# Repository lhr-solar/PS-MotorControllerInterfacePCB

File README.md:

# PS - Motor Controller Interface

## Board Specification
- Handles power conversion and fan control for the Prohelion WaveSculptor 22.

## Confluence
- https://cloud.wikis.utexas.edu/wiki/spaces/LHRSOLAR/pages/484769832/Motor+Controller+Interface+Board

## File Structure
- Core
- Drivers
- Tasks
- Tests
- Embedded-Sharepoint
- Makefile

## Building / Testing
- nix develop ./Embedded-Sharepoint (from firmware directory)
- Run ``` make ``` to build main files.
- Run ``` make TEST=test_name ```, where ```test_name``` is the name of the test without the .c suffix.

## Flashing (UART)
- Make sure switch is set to EXT, then flash via UART (``` make flash-uart ```). 
- Set the switch to USR then press RESET button to execute code.

- Note: flashing to this board (not psom issue) is really difficult. have fun spamming reset
## Flashing (ST-Link)
- To flash an STM32 microcontroller using an ST-Link, wire the device to the ST-Link (SWDIO, SWCLK, GND, 3.3V) and use software like STM32CubeProgrammer or STM32 ST-LINK Utility to erase, load, and verify the .bin or .hex firmware file.

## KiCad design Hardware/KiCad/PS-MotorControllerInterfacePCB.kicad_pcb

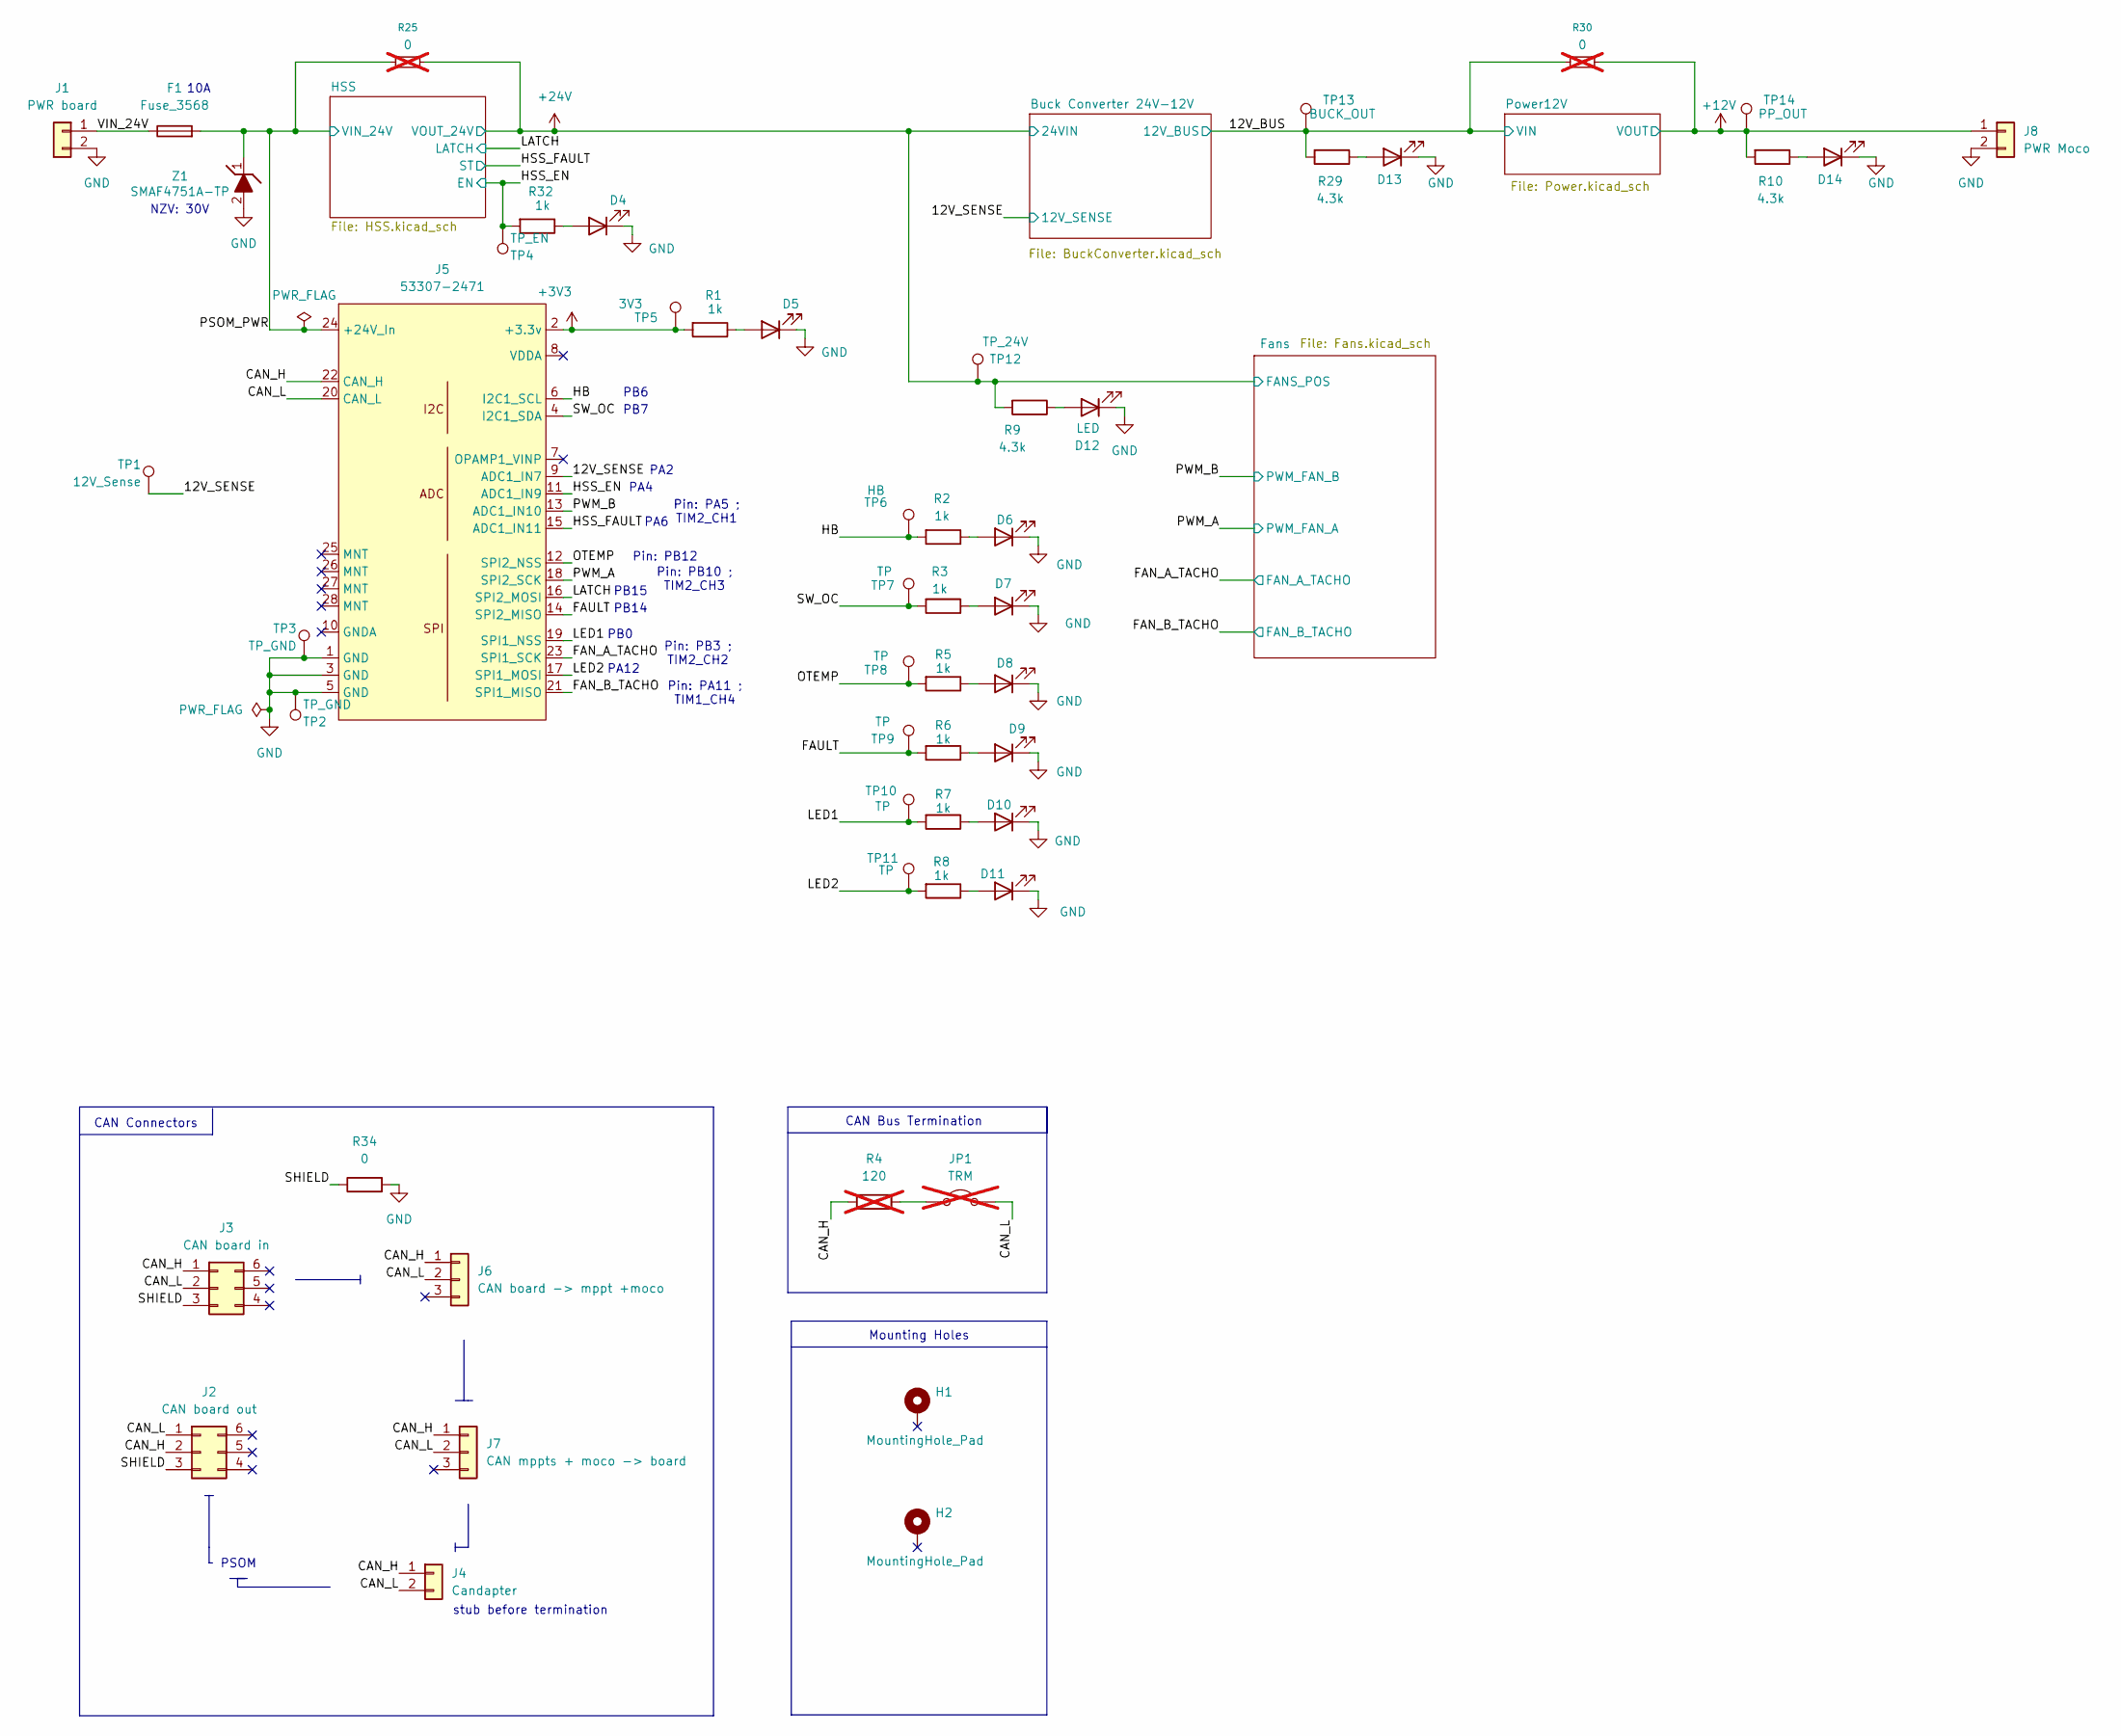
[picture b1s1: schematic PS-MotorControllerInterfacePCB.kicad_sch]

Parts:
D4, D5, D6, D7, D8, D9, D10, D11, D12, D13, D14: LED; LED_0603_1608Metric; LCSC C84263
F1: Fuse_3568; FUSE_3568; Mouser P/N 534-3568
H1, H2: MountingHole_Pad; MountingHole_3.2mm_M3_Pad_TopBottom
J1: PWR board; 105313-2102
J2: CAN board out; 105314-1306
J3: CAN board in; 105314-1306
J4: Candapter; 105313-2102
J5: 53307-2471; PeripheralSOM
J6: CAN board -> mppt +moco; 105313-1103
J7: CAN mppts + moco -> board; 105313-1103
J8: PWR Moco; 105313-2102
JP1: TRM; PinHeader_1x02_P2.54mm_Vertical; Mouser Part Number M7567-05; not fitted
R1, R2, R3, R5, R6, R7, R8, R32: 1k; R_0603_1608Metric_Pad0.98x0.95mm_HandSolder; Manufacturer_Part_Number CRCW06034K30FKEA; LCSC C21190
R4: 120; R_0603_1608Metric_Pad0.98x0.95mm_HandSolder; Manufacturer_Part_Number CRCW0603120RFKEC; LCSC C22787; not fitted
R9, R10, R29: 4.3k; R_0603_1608Metric_Pad0.98x0.95mm_HandSolder; Manufacturer_Part_Number CRCW06034K30FKEA; LCSC C2907165
R25, R30: 0; R_0603_1608Metric_Pad0.98x0.95mm_HandSolder; LCSC C21189; not fitted
R34: 0; R_0603_1608Metric_Pad0.98x0.95mm_HandSolder; LCSC C21189
TP1: 12V_Sense; TestPoint_Keystone_5000-5004_Miniature
TP2: TP_GND; PinHeader_1x01_P2.54mm_Vertical
TP3: TP_GND; TestPoint_Keystone_5000-5004_Miniature
TP4: TP_EN; TestPoint_Keystone_5000-5004_Miniature
TP5: 3V3; TestPoint_Keystone_5000-5004_Miniature
TP6: HB; TestPoint_Keystone_5000-5004_Miniature
TP7, TP8, TP9, TP10, TP11: TP; TestPoint_Keystone_5000-5004_Miniature
TP12: TP_24V; TestPoint_Keystone_5000-5004_Miniature
TP13: BUCK_OUT; TestPoint_Keystone_5000-5004_Miniature
TP14: PP_OUT; TestPoint_Keystone_5000-5004_Miniature
Z1: SMAF4751A-TP; SODFL5026X125N; Mouser Part Number 833-SMAF4751A-TP

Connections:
+3V3: J5.2 (+3.3v), R1.2, TP5.1; also elsewhere on the board
+12V: J8.1, R10.2, R30.2, TP14.1; also elsewhere on the board
+24V: R9.2, R25.2, TP12.1; also elsewhere on the board
/12V_BUS: R29.2, R30.1, TP13.1; also elsewhere on the board
/12V_SENSE: J5.9 (ADC1_IN7), TP1.1; also elsewhere on the board
/CAN_H: J2.2, J3.1, J4.1, J5.22 (CAN_H), J6.1, J7.1, R4.1
/CAN_L: J2.1, J3.2, J4.2, J5.20 (CAN_L), J6.2, J7.2, JP1.2 (B)
/FAN_A_TACHO: J5.23 (SPI1_SCK); also elsewhere on the board
/FAN_B_TACHO: J5.21 (SPI1_MISO); also elsewhere on the board
/FAULT: J5.14 (SPI2_MISO), R6.2, TP9.1
/HB: J5.6 (I2C1_SCL), R2.2, TP6.1
/HSS_EN: J5.11 (ADC1_IN9), R32.2, TP4.1; also elsewhere on the board
/HSS_FAULT: J5.15 (ADC1_IN11); also elsewhere on the board
/LATCH: J5.16 (SPI2_MOSI); also elsewhere on the board
/LED1: J5.19 (SPI1_NSS), R7.2, TP10.1
/LED2: J5.17 (SPI1_MOSI), R8.2, TP11.1
/OTEMP: J5.12 (SPI2_NSS), R5.2, TP8.1
/PSOM_PWR: F1.2, J5.24 (+24V_In), R25.1, Z1.1 (K); also elsewhere on the board
/PWM_A: J5.18 (SPI2_SCK); also elsewhere on the board
/PWM_B: J5.13 (ADC1_IN10); also elsewhere on the board
/SHIELD: J2.3, J3.3, R34.1
/SW_OC: J5.4 (I2C1_SDA), R3.2, TP7.1
/VIN_24V: F1.1, J1.1
GND: D4.1 (K), D5.1 (K), D6.1 (K), D7.1 (K), D8.1 (K), D9.1 (K), D10.1 (K), D11.1 (K), D12.1 (K), D13.1 (K), D14.1 (K), J1.2, J5.1 (GND), J5.3 (GND), J5.5 (GND), J8.2, R34.2, TP2.1, TP3.1, Z1.2 (A); also elsewhere on the board
unnamed: D4.2 (A), R32.1
unnamed: D5.2 (A), R1.1
unnamed: D6.2 (A), R2.1
unnamed: D7.2 (A), R3.1
unnamed: D8.2 (A), R5.1
unnamed: D9.2 (A), R6.1
unnamed: D10.2 (A), R7.1
unnamed: D11.2 (A), R8.1
unnamed: D12.2 (A), R9.1
unnamed: D13.2 (A), R29.1
unnamed: D14.2 (A), R10.1
unnamed: JP1.1 (A), R4.2

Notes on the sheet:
NZV: 30V
PSOM
CAN Bus Termination
PA4
PB15
Pin: PB10 ; TIM2_CH3
PB6
10A
Pin: PA11 ; TIM1_CH4
PB7
CAN Connectors
Mounting Holes
Pin: PB12
stub before termination
Pin: PA5 ; TIM2_CH1
Pin: PB3 ; TIM2_CH2
PA2
PA12
PB14
PA6
PB0

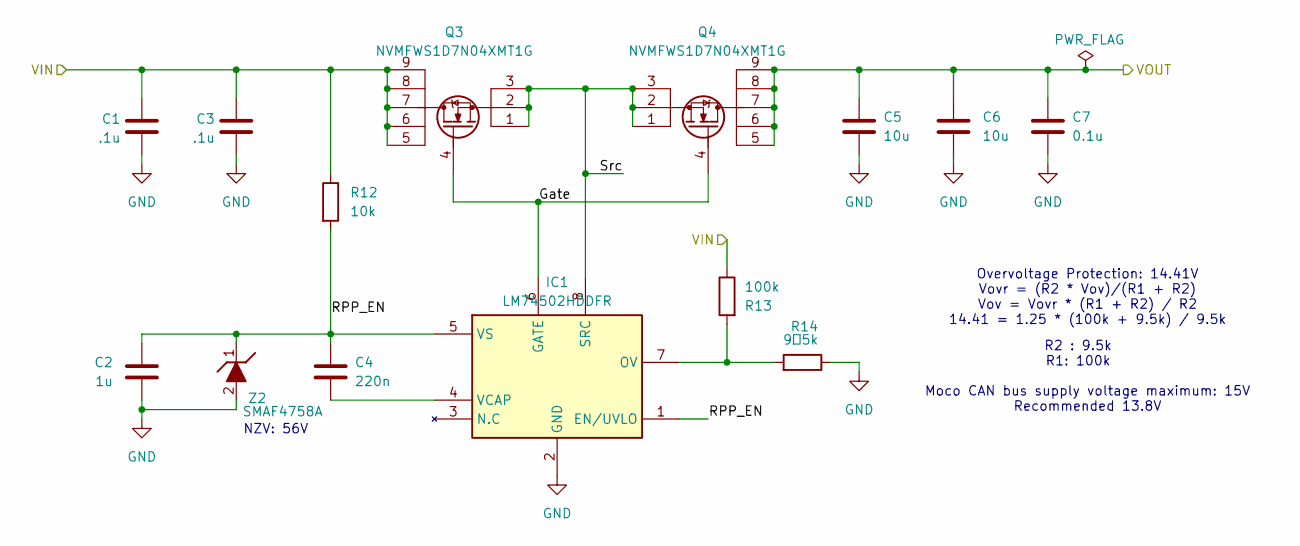
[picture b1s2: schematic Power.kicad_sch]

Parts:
C1, C3: .1u; C_0603_1608Metric_Pad1.08x0.95mm_HandSolder; Manufacturer_Part_Number 06035C223K4T4A; LCSC C14663
C2: 1u; C_0603_1608Metric_Pad1.08x0.95mm_HandSolder; Manufacturer_Part_Number MLASU168SB5105KTNA01; LCSC C15849
C4: 220n; C_0603_1608Metric_Pad1.08x0.95mm_HandSolder; Manufacturer_Part_Number MSASU168SB7224KTNB25; LCSC C344195
C5, C6: 10u; C_0603_1608Metric_Pad1.08x0.95mm_HandSolder; Manufacturer_Part_Number GRM21BR61H106KE43K; LCSC C1691
C7: 0.1u; C_0603_1608Metric_Pad1.08x0.95mm_HandSolder; Manufacturer_Part_Number MLASH168SB7104KTNA01; LCSC C14663
IC1: LM74502HDDFR; SOT65P280X110-8N; Mouser Part Number 595-LM74502HDDFR
Q3, Q4: NVMFWS1D7N04XMT1G; NVMFWS3D0P04M8LT1G; LCSC P/N C133142
R12: 10k; R_0805_2012Metric_Pad1.20x1.40mm_HandSolder; Manufacturer_Part_Number CRCW060310K0FKEI; LCSC C702829
R13: 100k; R_0603_1608Metric_Pad0.98x0.95mm_HandSolder; Manufacturer_Part_Number CRCW0603100KFKEE; LCSC C25803
R14: 9。5k; R_0603_1608Metric_Pad0.98x0.95mm_HandSolder
Z2: SMAF4758A; SODFL5026X125N; Manufacturer_Part_Number SMAF4749A-TP; LCSC C183490

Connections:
+12V: C5.1, C6.1, C7.1, Q4.5, Q4.6, Q4.7, Q4.8, Q4.9; also elsewhere on the board
/12V_BUS: C1.2, C3.2, Q3.5, Q3.6, Q3.7, Q3.8, Q3.9, R12.1, R13.1; also elsewhere on the board
/Power12V/Gate: IC1.6 (GATE), Q3.4, Q4.4
/Power12V/RPP_EN: C2.2, C4.1, IC1.1 (EN/UVLO), IC1.5 (VS), R12.2, Z2.1 (K)
/Power12V/Src: IC1.8 (SRC), Q3.1, Q3.2, Q3.3, Q4.1, Q4.2, Q4.3
GND: C1.1, C2.1, C3.1, C5.2, C6.2, C7.2, IC1.2 (GND), R14.1, Z2.2 (A); also elsewhere on the board
unnamed: IC1.7 (OV), R13.2, R14.2
unnamed: C4.2, IC1.4 (VCAP)

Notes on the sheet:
Overvoltage Protection: 14.41V Vovr = (R2 * Vov)/(R1 + R2) Vov = Vovr * (R1 + R2) / R2 14.41 = 1.25 * (100k + 9.5k) / 9.5k
Moco CAN bus supply voltage maximum: 15V Recommended 13.8V
R2 : 9.5k R1: 100k
NZV: 56V

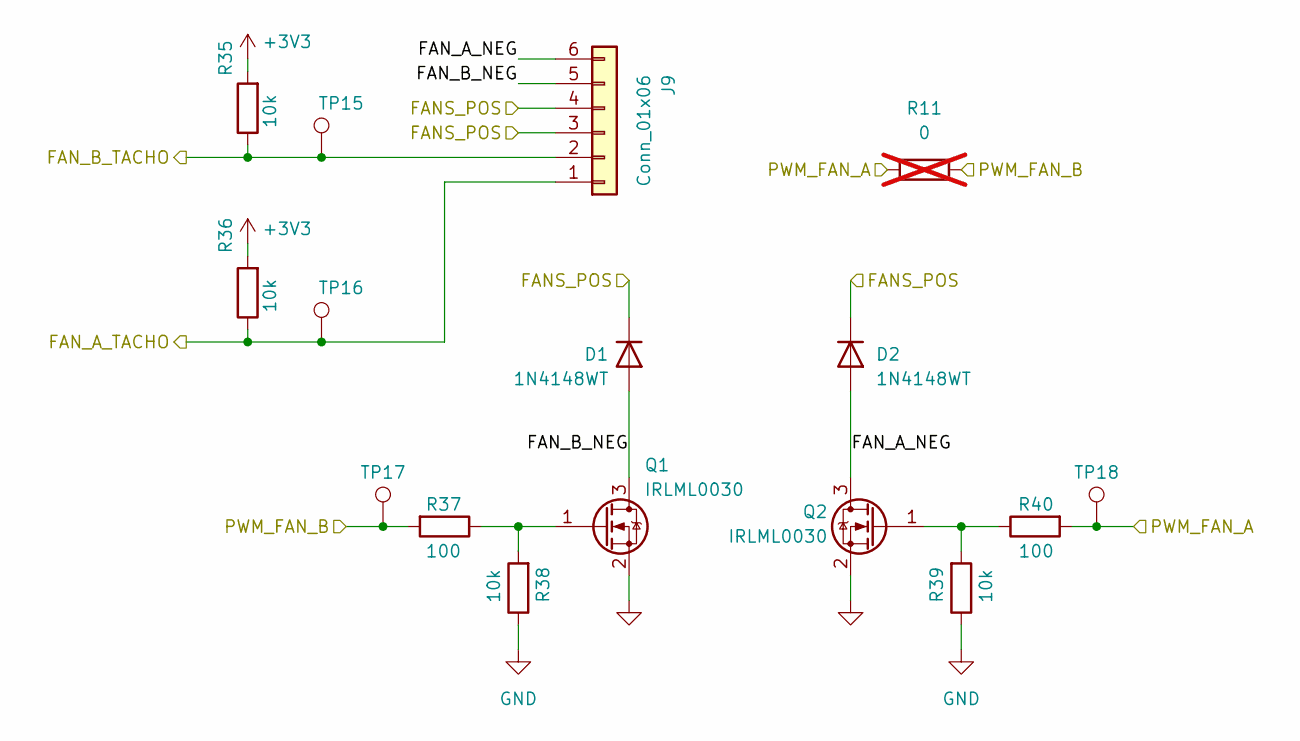
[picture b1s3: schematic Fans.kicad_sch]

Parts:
D1, D2: 1N4148WT; SODFL4724X108N; Manufacturer_Part_Number NCD0603R1; Mouser Part Number 637-1N4148WT
J9: Conn_01x06; 105313-1106; Mouser Part Number 538-105309-1206
Q1, Q2: IRLML0030; SOT-23; LCSC C67272
R11: 0; R_0603_1608Metric_Pad0.98x0.95mm_HandSolder; Manufacturer_Part_Number CRCW06030000Z0EE; LCSC C21189; not fitted
R35, R36, R38, R39: 10k; R_0603_1608Metric_Pad0.98x0.95mm_HandSolder; Manufacturer_Part_Number CRCW060310K0FKEI; LCSC C25804
R37, R40: 100; R_0603_1608Metric_Pad0.98x0.95mm_HandSolder; Manufacturer_Part_Number CRCW0603120RFKEC; LCSC C22356636
TP15, TP16: TP_PWM_B; TestPoint_Pad_1.0x1.0mm
TP17: TP_PWM_A; PinHeader_1x01_P2.54mm_Vertical
TP18: TP_PWM_B; PinHeader_1x01_P2.54mm_Vertical

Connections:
+3V3: R35.2, R36.2; also elsewhere on the board
+24V: D1.1 (K), D2.1 (K), J9.3, J9.4; also elsewhere on the board
/FAN_A_TACHO: J9.1, R36.1, TP16.1; also elsewhere on the board
/FAN_B_TACHO: J9.2, R35.1, TP15.1; also elsewhere on the board
/Fans/FAN_A_NEG: D2.2 (A), J9.6, Q2.3 (D)
/Fans/FAN_B_NEG: D1.2 (A), J9.5, Q1.3 (D)
/PWM_A: R11.1, R40.2, TP18.1; also elsewhere on the board
/PWM_B: R11.2, R37.2, TP17.1; also elsewhere on the board
GND: Q1.2 (S), Q2.2 (S), R38.1, R39.1; also elsewhere on the board
unnamed: Q1.1 (G), R37.1, R38.2
unnamed: Q2.1 (G), R39.2, R40.1

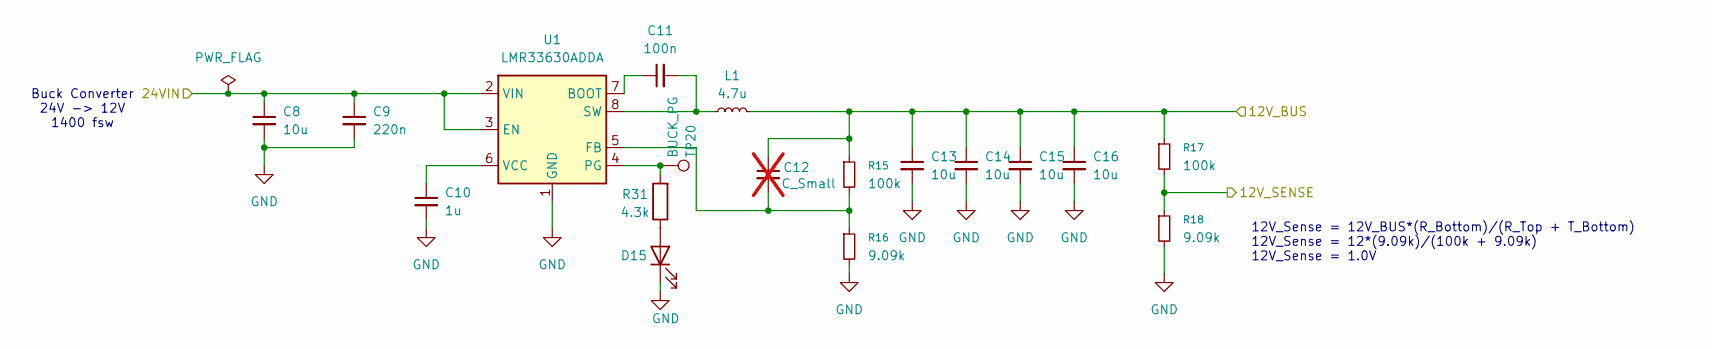
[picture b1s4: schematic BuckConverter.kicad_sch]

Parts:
C8, C13, C14, C15, C16: 10u; C_0603_1608Metric_Pad1.08x0.95mm_HandSolder; LCSC C1691
C9: 220n; C_0603_1608Metric_Pad1.08x0.95mm_HandSolder; LCSC C344195
C10: 1u; C_0603_1608Metric_Pad1.08x0.95mm_HandSolder; LCSC C15849
C11: 100n; C_0603_1608Metric_Pad1.08x0.95mm_HandSolder; LCSC C14663
C12: C_Small; C_0603_1608Metric_Pad1.08x0.95mm_HandSolder; not fitted
D15: LED; LED_0603_1608Metric; LCSC C84263
L1: 4.7u; IND-SMD_L5.0-W5.0; LCSC C354606
R15, R17: 100k; R_0603_1608Metric_Pad0.98x0.95mm_HandSolder; LCSC C25803
R16, R18: 9.09k; R_0603_1608Metric_Pad0.98x0.95mm_HandSolder
R31: 4.3k; R_0603_1608Metric_Pad0.98x0.95mm_HandSolder; Manufacturer_Part_Number CRCW06034K30FKEA; LCSC C2907165
TP20: BUCK_PG; TestPoint_Keystone_5000-5004_Miniature
U1: LMR33630ADDA; Texas_HSOP-8-1EP_3.9x4.9mm_P1.27mm_ThermalVias; LCSC C841384

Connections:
+24V: C8.1, C9.1, U1.2 (VIN), U1.3 (EN); also elsewhere on the board
/12V_BUS: C12.1, C13.1, C14.1, C15.1, C16.1, L1.2, R15.1, R17.1; also elsewhere on the board
/12V_SENSE: R17.2, R18.1; also elsewhere on the board
GND: C8.2, C9.2, C10.2, C13.2, C14.2, C15.2, C16.2, D15.1 (K), R16.2, R18.2, U1.1 (GND), U1.9 (GND); also elsewhere on the board
unnamed: D15.2 (A), R31.1
unnamed: C11.1, U1.7 (BOOT)
unnamed: C12.2, R15.2, R16.1, U1.5 (FB)
unnamed: R31.2, TP20.1, U1.4 (PG)
unnamed: C11.2, L1.1, U1.8 (SW)
unnamed: C10.1, U1.6 (VCC)

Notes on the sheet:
12V_Sense = 12V_BUS*(R_Bottom)/(R_Top + T_Bottom) 12V_Sense = 12*(9.09k)/(100k + 9.09k) 12V_Sense = 1.0V
Buck Converter 24V -> 12V 1400 fsw

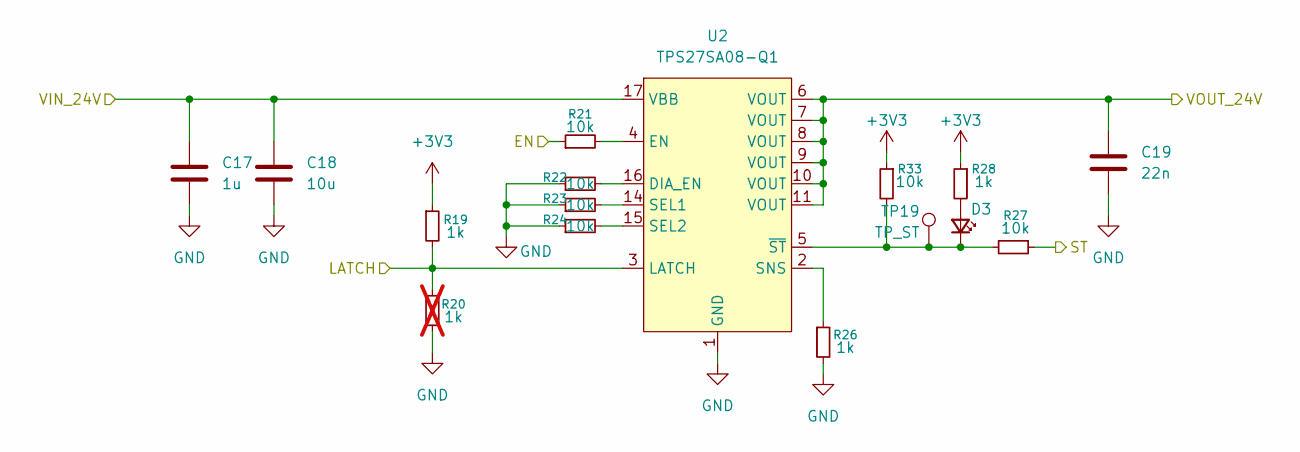
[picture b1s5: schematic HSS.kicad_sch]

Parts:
C17: 1u; C_0603_1608Metric_Pad1.08x0.95mm_HandSolder; LCSC C15849
C18: 10u; C_0805_2012Metric_Pad1.18x1.45mm_HandSolder; LCSC C440198
C19: 22n; C_0603_1608Metric_Pad1.08x0.95mm_HandSolder; LCSC C21122
D3: LED_Small; LED_0603_1608Metric; LCSC C84263
R19, R26, R28: 1k; R_0603_1608Metric_Pad0.98x0.95mm_HandSolder; LCSC C21190
R20: 1k; R_0603_1608Metric_Pad0.98x0.95mm_HandSolder; LCSC C21190; not fitted
R21, R22, R23, R24, R27, R33: 10k; R_0603_1608Metric_Pad0.98x0.95mm_HandSolder; LCSC C25804
TP19: TP_ST; TestPoint_Keystone_5000-5004_Miniature
U2: TPS27SA08-Q1; HTSSOP-16-1EP_4.4x5mm_P0.65mm_EP3.4x5mm_Mask2.66x2.46mm_The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; LCSC C2870129

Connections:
+3V3: R19.1, R28.1, R33.1; also elsewhere on the board
+24V: C19.1, U2.6 (VOUT), U2.7 (VOUT), U2.8 (VOUT), U2.9 (VOUT), U2.10 (VOUT), U2.11 (VOUT); also elsewhere on the board
/HSS_EN: R21.1; also elsewhere on the board
/HSS_FAULT: R27.1; also elsewhere on the board
/LATCH: R19.2, R20.2, U2.3 (LATCH); also elsewhere on the board
/PSOM_PWR: C17.1, C18.1, U2.17 (VBB); also elsewhere on the board
GND: C17.2, C18.2, C19.2, R20.1, R22.1, R23.1, R24.1, R26.2, U2.1 (GND); also elsewhere on the board
unnamed: D3.2 (A), R28.2
unnamed: D3.1 (K), R27.2, R33.2, TP19.1, U2.5 (~ST)
unnamed: R22.2, U2.16 (DIA_EN)
unnamed: R21.2, U2.4 (EN)
unnamed: R23.2, U2.14 (SEL1)
unnamed: R24.2, U2.15 (SEL2)
unnamed: R26.1, U2.2 (SNS)

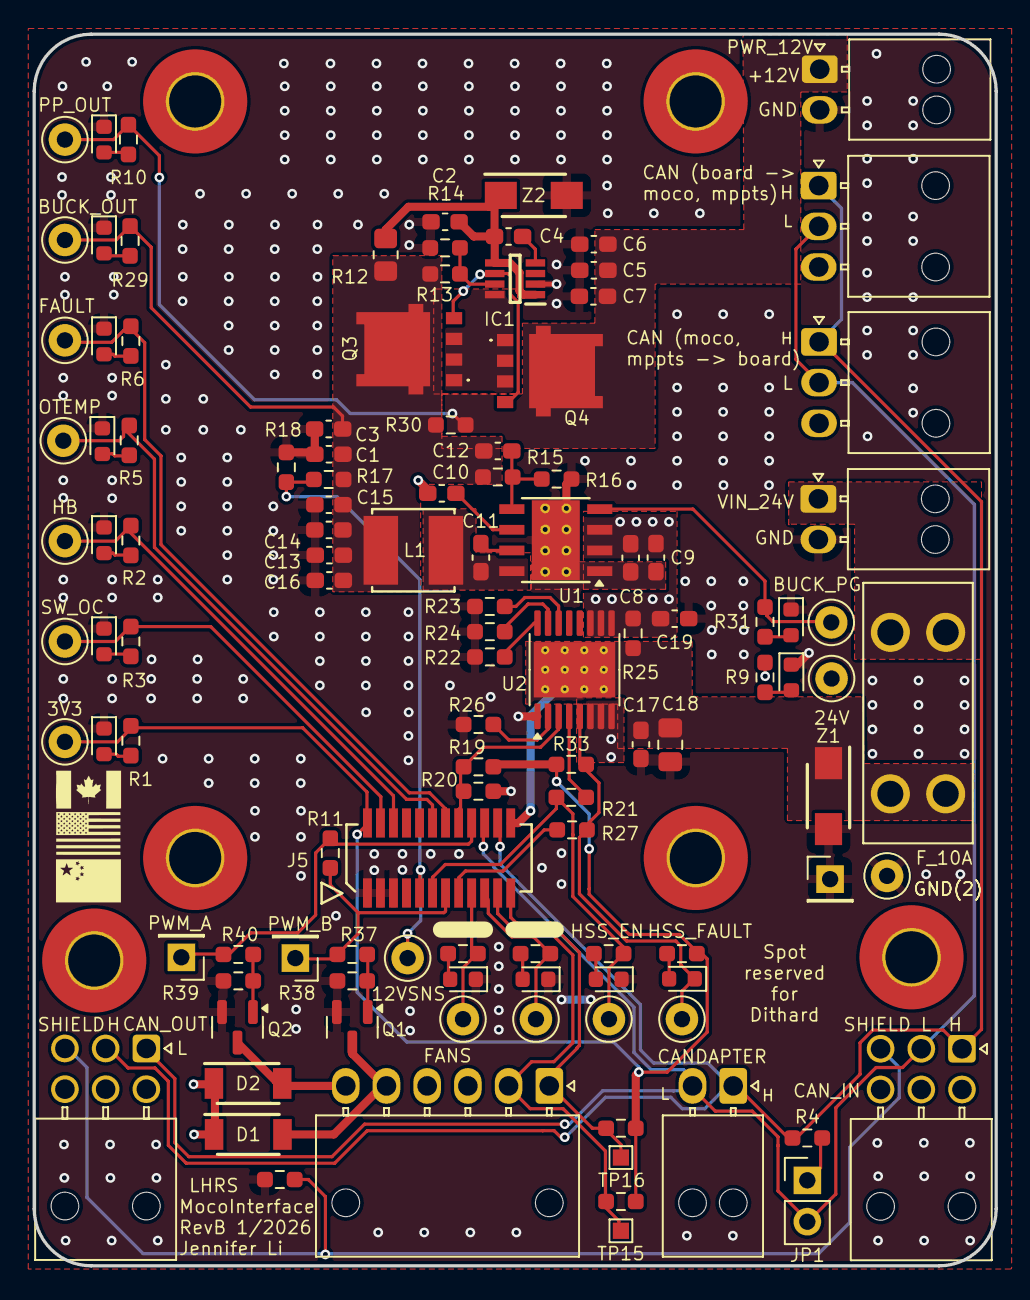
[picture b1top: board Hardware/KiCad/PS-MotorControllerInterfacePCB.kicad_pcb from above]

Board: 2 copper layers, 59.1 x 75.7 mm, 117 parts (0 on the bottom side), 58 nets.

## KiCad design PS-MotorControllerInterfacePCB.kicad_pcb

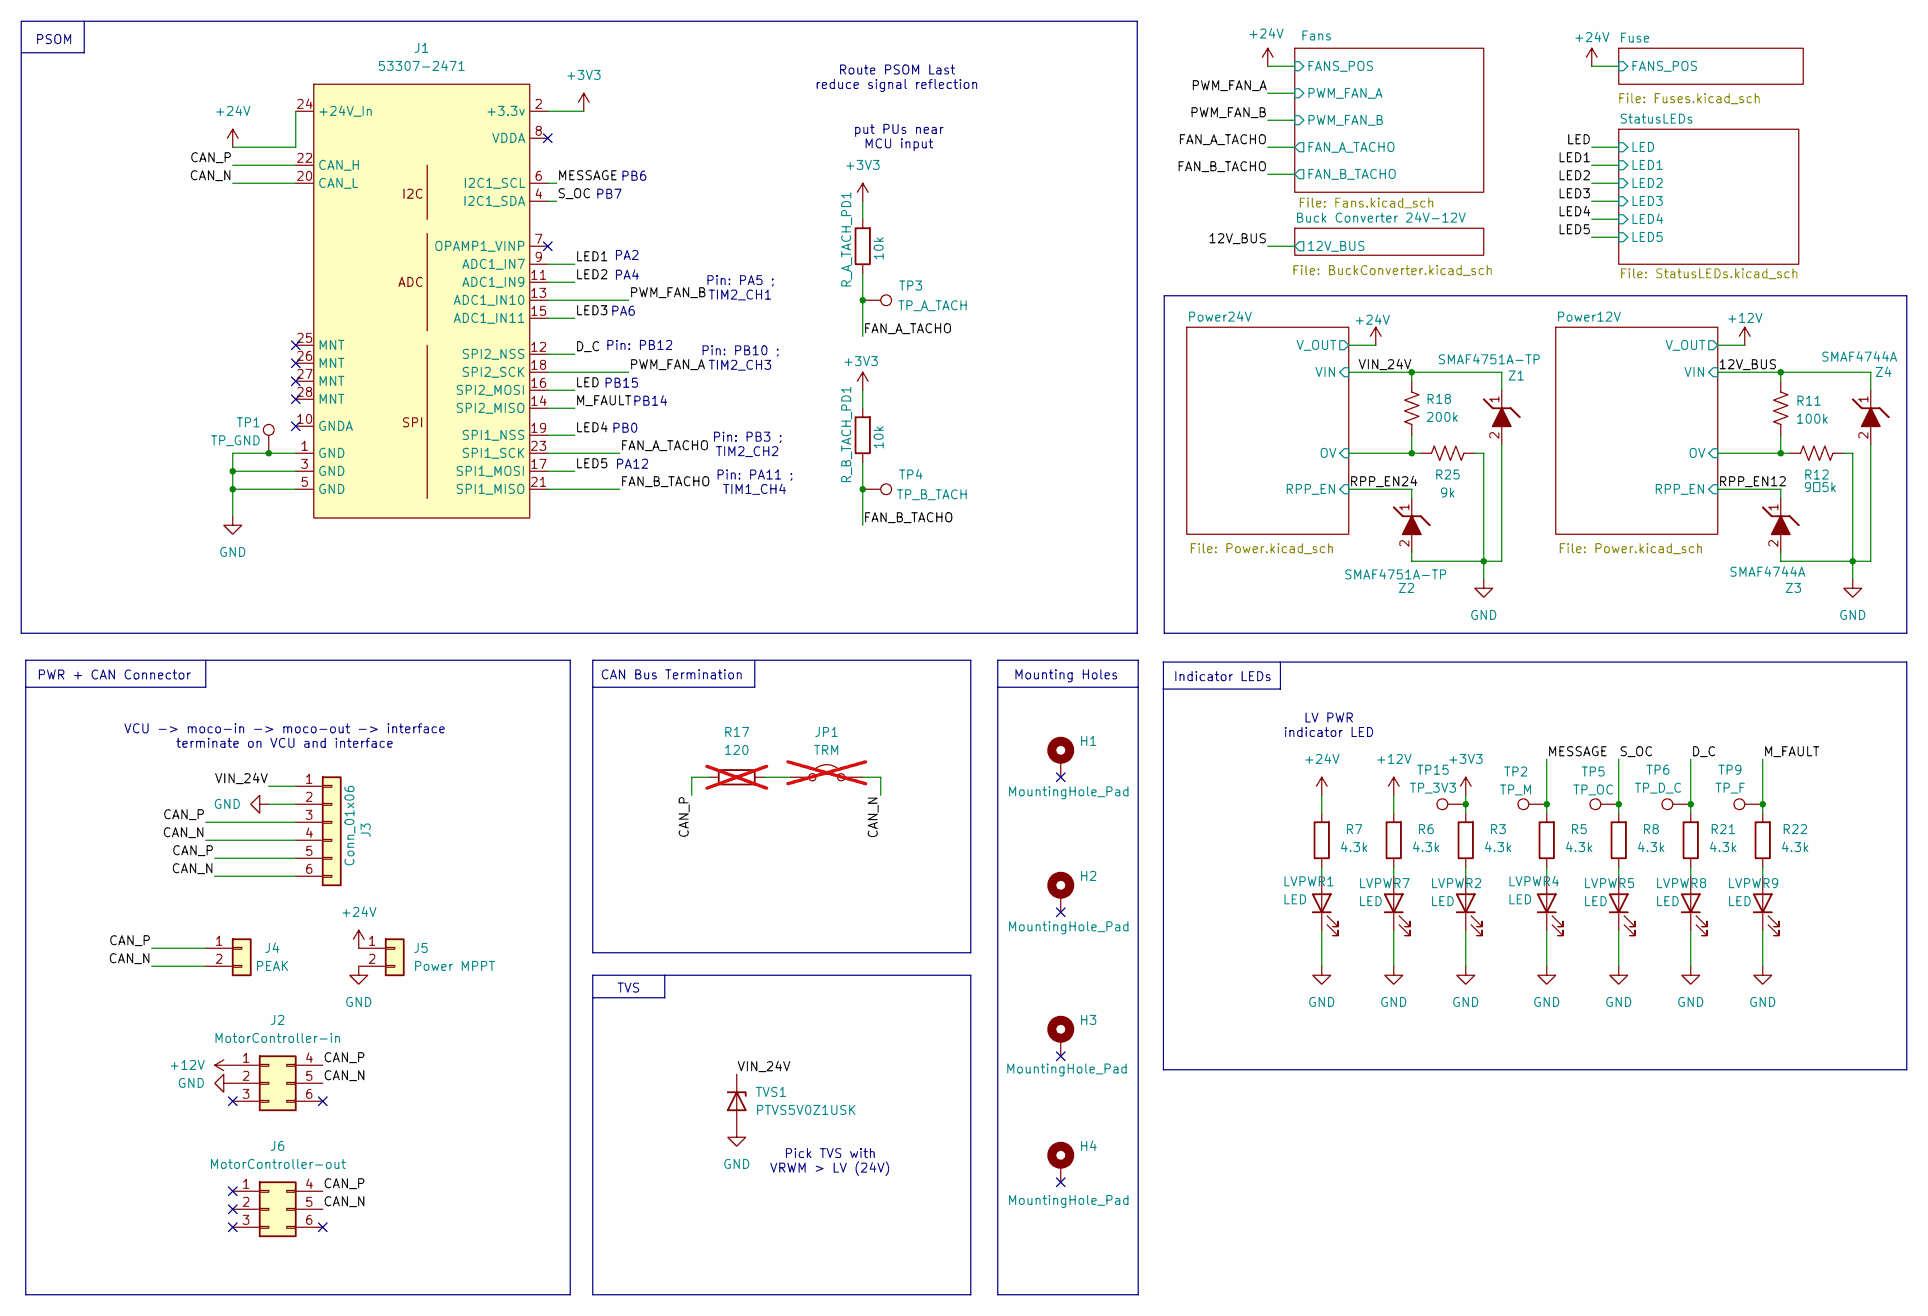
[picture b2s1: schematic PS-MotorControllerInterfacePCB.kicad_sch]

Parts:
H1, H2, H3, H4: MountingHole_Pad; MountingHole_3.2mm_M3
J1: 53307-2471; PeripheralSOM
J2: MotorController-in; Molex_Microfit3.0_02x03_6-Pin-Vertical-PCB-Receptacle_44769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
J3: Conn_01x06; Molex_Nano-Fit_105309-xx06_1x06_P2.50mm_Vertical
J4: PEAK; Molex_Nano-Fit_105309-xx02_1x02_P2.50mm_Vertical
J5: Power MPPT; Molex_Nano-Fit_105309-xx02_1x02_P2.50mm_Vertical
J6: MotorController-out; Molex_Microfit3.0_02x03_6-Pin-Vertical-PCB-Receptacle_44769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
JP1: TRM; PinHeader_1x02_P2.54mm_Vertical; not fitted
LVPWR1, LVPWR2, LVPWR4, LVPWR5, LVPWR7, LVPWR8, LVPWR9: LED; LED_0603_1608Metric
R3, R5, R6, R7, R8, R21, R22: 4.3k; R_0603_1608Metric_Pad0.98x0.95mm_HandSolder; Manufacturer_Part_Number CRCW06034K30FKEA
R11: 100k; R_0603_1608Metric_Pad0.98x0.95mm_HandSolder; Manufacturer_Part_Number CRCW0603100KFKEE
R12: 9。5k; R_0603_1608Metric_Pad0.98x0.95mm_HandSolder
R17: 120; R_0603_1608Metric_Pad0.98x0.95mm_HandSolder; Manufacturer_Part_Number CRCW0603120RFKEC; not fitted
R18: 200k; R_0603_1608Metric_Pad0.98x0.95mm_HandSolder; Manufacturer_Part_Number MCT06030C2003FP500
R25: 9k; R_0603_1608Metric_Pad0.98x0.95mm_HandSolder
R_A_TACH_PD1: 10k; R_0603_1608Metric_Pad0.98x0.95mm_HandSolder; Manufacturer_Part_Number CRCW060310K0FKEI
R_B_TACH_PD1: 10k; R_0603_1608Metric_Pad0.98x0.95mm_HandSolder; Manufacturer_Part_Number CRCW060310K0FKEI
TP1: TP_GND; TestPoint_Pad_1.0x1.0mm
TP2: TP_M; TestPoint_Pad_1.0x1.0mm
TP3: TP_A_TACH; TestPoint_Pad_1.0x1.0mm
TP4: TP_B_TACH; TestPoint_Pad_1.0x1.0mm
TP5: TP_OC; TestPoint_Pad_1.0x1.0mm
TP6: TP_D_C; TestPoint_Pad_1.0x1.0mm
TP9: TP_F; TestPoint_Pad_1.0x1.0mm
TP15: TP_3V3; TestPoint_Pad_1.0x1.0mm
TVS1: PTVS5V0Z1USK; Nexperia_DSN1608-2_1.6x0.8mm
Z1, Z2: SMAF4751A-TP; SODFL5026X125N; Mouser Part Number 833-SMAF4749A-TP
Z3, Z4: SMAF4744A; SODFL5026X125N; Mouser Part Number 833-SMAF4749A-TP

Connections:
+3V3: J1.2 (+3.3v), R3.2, R_A_TACH_PD1.2, R_B_TACH_PD1.2, TP15.1
+12V: J2.1, R6.2; also elsewhere on the board
+24V: J1.24 (+24V_In), J5.1, R7.2; also elsewhere on the board
/12V_BUS: R11.1, Z4.1 (K); also elsewhere on the board
/CAN_N: J1.20 (CAN_L), J2.5, J3.4, J3.6, J4.2, J6.5, JP1.2 (B)
/CAN_P: J1.22 (CAN_H), J2.4, J3.3, J3.5, J4.1, J6.4, R17.1
/D_C: J1.12 (SPI2_NSS), R21.2, TP6.1
/FAN_A_TACHO: J1.23 (SPI1_SCK), R_A_TACH_PD1.1, TP3.1; also elsewhere on the board
/FAN_B_TACHO: J1.21 (SPI1_MISO), R_B_TACH_PD1.1, TP4.1; also elsewhere on the board
/LED: J1.16 (SPI2_MOSI); also elsewhere on the board
/LED1: J1.9 (ADC1_IN7); also elsewhere on the board
/LED2: J1.11 (ADC1_IN9); also elsewhere on the board
/LED3: J1.15 (ADC1_IN11); also elsewhere on the board
/LED4: J1.19 (SPI1_NSS); also elsewhere on the board
/LED5: J1.17 (SPI1_MOSI); also elsewhere on the board
/MESSAGE: J1.6 (I2C1_SCL), R5.2, TP2.1
/M_FAULT: J1.14 (SPI2_MISO), R22.2, TP9.1
/PWM_FAN_A: J1.18 (SPI2_SCK); also elsewhere on the board
/PWM_FAN_B: J1.13 (ADC1_IN10); also elsewhere on the board
/Power12V/OV: R11.2, R12.1; also elsewhere on the board
/Power24V/OV: R18.2, R25.1; also elsewhere on the board
/RPP_EN12: Z3.1 (K); also elsewhere on the board
/RPP_EN24: Z2.1 (K); also elsewhere on the board
/S_OC: J1.4 (I2C1_SDA), R8.2, TP5.1
/VIN_24V: J3.1, R18.1, TVS1.1 (K), Z1.1 (K); also elsewhere on the board
GND: J1.1 (GND), J1.3 (GND), J1.5 (GND), J2.2, J3.2, J5.2, LVPWR1.1 (K), LVPWR2.1 (K), LVPWR4.1 (K), LVPWR5.1 (K), LVPWR7.1 (K), LVPWR8.1 (K), LVPWR9.1 (K), R12.2, R25.2, TP1.1, TVS1.2 (A), Z1.2 (A), Z2.2 (A), Z3.2 (A), Z4.2 (A); also elsewhere on the board
unnamed: JP1.1 (A), R17.2
unnamed: LVPWR1.2 (A), R7.1
unnamed: LVPWR2.2 (A), R3.1
unnamed: LVPWR4.2 (A), R5.1
unnamed: LVPWR5.2 (A), R8.1
unnamed: LVPWR7.2 (A), R6.1
unnamed: LVPWR8.2 (A), R21.1
unnamed: LVPWR9.2 (A), R22.1

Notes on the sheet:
put PUs near MCU input
Pick TVS with VRWM > LV (24V)
CAN Bus Termination
PA4
PB15
Pin: PB10 ; TIM2_CH3
PB6
TVS
Pin: PA11 ; TIM1_CH4
PB7
PWR + CAN Connector
Mounting Holes
LV PWR indicator LED
Pin: PB12
Route PSOM Last reduce signal reflection
Pin: PA5 ; TIM2_CH1
Pin: PB3 ; TIM2_CH2
PA2
PSOM
PA12
PB14
VCU -> moco-in -> moco-out -> interface terminate on VCU and interface
Indicator LEDs
PA6
PB0

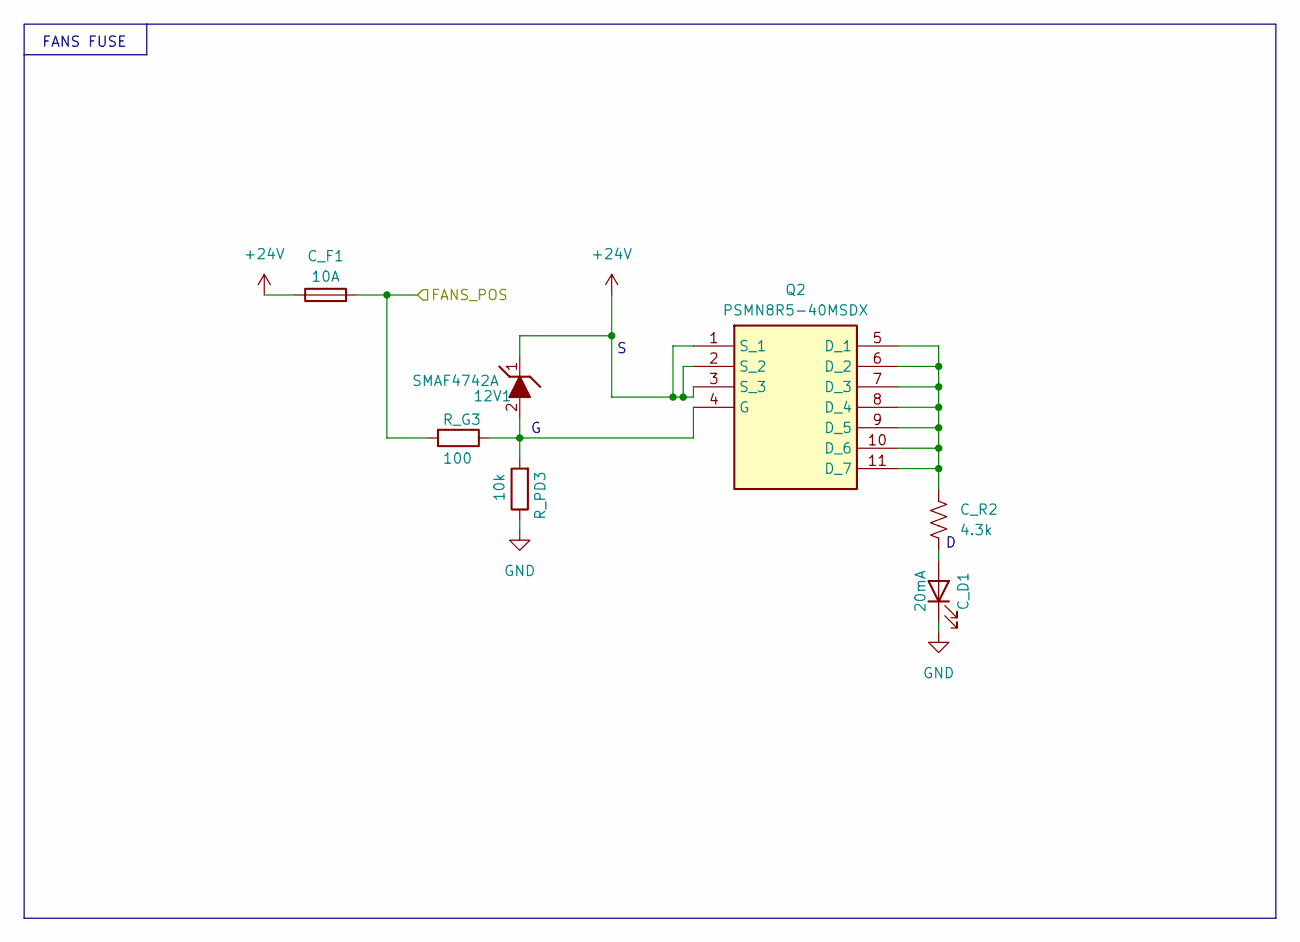
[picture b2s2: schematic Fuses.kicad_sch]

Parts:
12V1: SMAF4742A; SODFL5026X125N; Mouser Part Number 833-SMAF4749A-TP
C_D1: 20mA; LED_0805_2012Metric
C_F1: 10A; FUSE_3568
C_R2: 4.3k; R_0805_2012Metric; Manufacturer_Part_Number CRCW06034K30FKEA
Q2: PSMN8R5-40MSDX; Mouser Part Number 771-PSMN8R5-40MSDX
R_G3: 100; R_0603_1608Metric_Pad0.98x0.95mm_HandSolder; Manufacturer_Part_Number CRCW0603120RFKEC
R_PD3: 10k; R_0603_1608Metric_Pad0.98x0.95mm_HandSolder; Manufacturer_Part_Number CRCW060310K0FKEI

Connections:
+24V: 12V1.1 (K), C_F1.1, C_F1.2, Q2.1 (S_1), Q2.2 (S_2), Q2.3 (S_3), R_G3.2; also elsewhere on the board
GND: C_D1.1 (K), R_PD3.1; also elsewhere on the board
unnamed: 12V1.2 (A), Q2.4 (G), R_G3.1, R_PD3.2
unnamed: C_D1.2 (A), C_R2.2
unnamed: C_R2.1, Q2.5 (D_1), Q2.6 (D_2), Q2.7 (D_3), Q2.8 (D_4), Q2.9 (D_5), Q2.10 (D_6), Q2.11 (D_7)

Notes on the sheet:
FANS FUSE
